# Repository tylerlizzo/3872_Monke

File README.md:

# Monke
# File Structure

CAD - Includes files for 3D printed parts of the monkey

Docs - Relevant documentation for creating your own monkey

Firmware - Signal processing, selection of octave, manual control

Hardware - Arduino UNO shield for power distribution, motor control, microphone and speaker amplification, and digital-to-audio conversion

Production - Gerber files for board production and .stl files for enclosure

Simulation - Relevant files for verification of hardware

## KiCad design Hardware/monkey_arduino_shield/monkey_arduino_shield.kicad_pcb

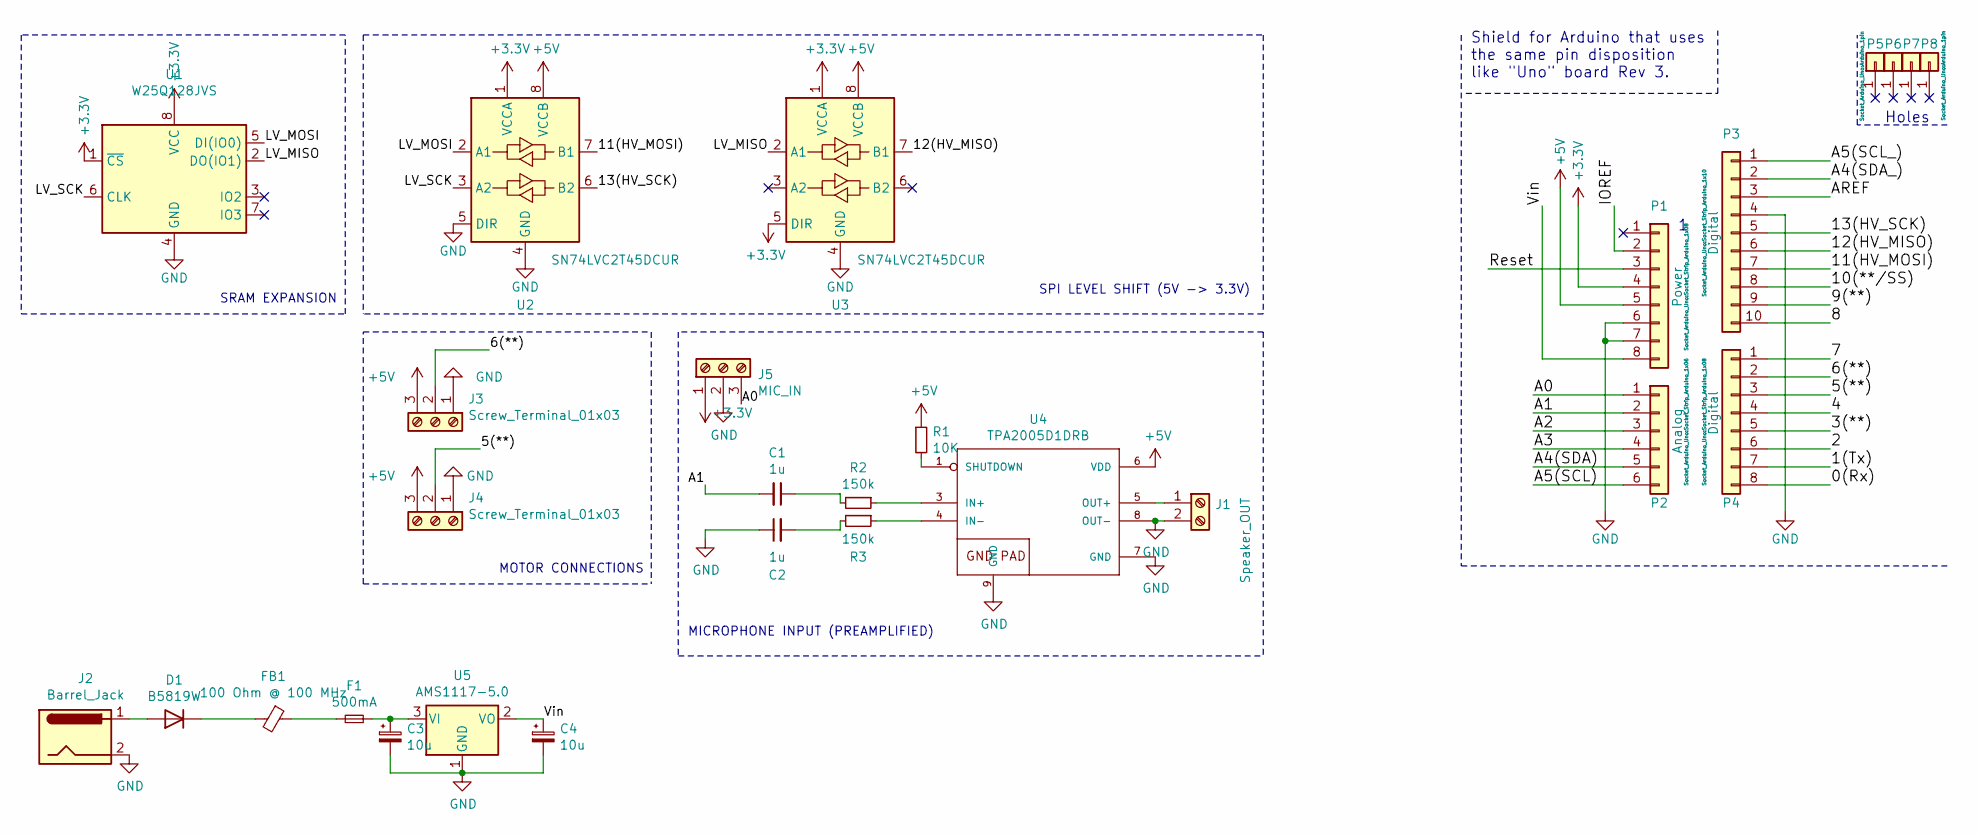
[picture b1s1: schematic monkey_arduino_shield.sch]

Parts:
C1, C2: 1u; C_1206_3216Metric
C3, C4: 10u; C_1206_3216Metric
D1: B5819W; D_0603_1608Metric
F1: 500mA; Fuse_0603_1608Metric
FB1: 100 Ohm @ 100 MHz; L_0201_0603Metric
J1: Speaker_OUT; TerminalBlock_bornier-2_P5.08mm
J2: Barrel_Jack; BarrelJack_Horizontal
J3, J4: Screw_Terminal_01x03; TerminalBlock_bornier-3_P5.08mm
J5: MIC_IN; TerminalBlock_bornier-3_P5.08mm
P1: Power; Socket_Strip_Arduino_1x08
P2: Analog; Socket_Strip_Arduino_1x06
P3: Digital; Socket_Strip_Arduino_1x10
P4: Digital; Socket_Strip_Arduino_1x08
P5, P6, P7, P8: CONN_01X01; Arduino_1pin
R1: 10K; R_0603_1608Metric
R2, R3: 150k; R_0603_1608Metric
U1: W25Q128JVS; SOIC-8_5.23x5.23mm_P1.27mm
U2, U3: SN74LVC2T45DCUR; VSSOP-8_2.4x2.1mm_P0.5mm
U4: TPA2005D1DRB; MSOP-8-1EP_3x3mm_P0.65mm_EP1.68x1.88mm
U5: AMS1117-5.0; SOT-223-3_TabPin2

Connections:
+3V3: J5.1, P1.4, U1.1 (~CS), U1.8 (VCC), U2.1 (VCCA), U3.1 (VCCA), U3.5 (DIR)
+5V: J3.3, J4.3, P1.5, R1.1, U2.8 (VCCB), U3.8 (VCCB), U4.6 (VDD)
/0(Rx): P4.8
/1(Tx): P4.7
/2: P4.6
/3(**): P4.5
/4: P4.4
/5(**): J4.2, P4.3
/6(**): J3.2, P4.2
/7: P4.1
/8: P3.10
/9(**): P3.9
/10(**/SS): P3.8
/11(HV_MOSI): P3.7, U2.7 (B1)
/12(HV_MISO): P3.6, U3.7 (B1)
/13(HV_SCK): P3.5, U2.6 (B2)
/A0: J5.3, P2.1
/A1: C1.2, P2.2
/A2: P2.3
/A3: P2.4
/A4(SDA): P2.5
/A4(SDA_): P3.2
/A5(SCL): P2.6
/A5(SCL_): P3.1
/AREF: P3.3
/IOREF: P1.2
/LV_MISO: U1.2 (DO(IO1)), U3.2 (A1)
/LV_MOSI: U1.5 (DI(IO0)), U2.2 (A1)
/LV_SCK: U1.6 (CLK), U2.3 (A2)
/Reset: P1.3
/Vin: C4.1, P1.8, U5.2 (VO)
GND: C2.1, C3.2, C4.2, J1.2, J2.2, J3.1, J4.1, J5.2, P1.6, P1.7, P3.4, U1.4 (GND), U2.4 (GND), U2.5 (DIR), U3.4 (GND), U4.7 (GND), U4.8 (OUT-), U4.9 (GND), U4.10 (GND), U4.11 (GND), U4.12 (GND), U4.13 (GND), U5.1 (GND)
unnamed: C1.1, R2.2
unnamed: C2.2, R3.2
unnamed: C3.1, F1.2, U5.3 (VI)
unnamed: D1.1 (K), FB1.2
unnamed: D1.2 (A), J2.1
unnamed: F1.1, FB1.1
unnamed: J1.1, U4.5 (OUT+)
unnamed: R1.2, U4.1 (SHUTDOWN)
unnamed: R2.1, U4.3 (IN+)
unnamed: R3.1, U4.4 (IN-)

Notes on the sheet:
Holes
Shield for Arduino that uses the same pin disposition like "Uno" board Rev 3.
SRAM EXPANSION
SPI LEVEL SHIFT (5V -> 3.3V)
MOTOR CONNECTIONS
MICROPHONE INPUT (PREAMPLIFIED)

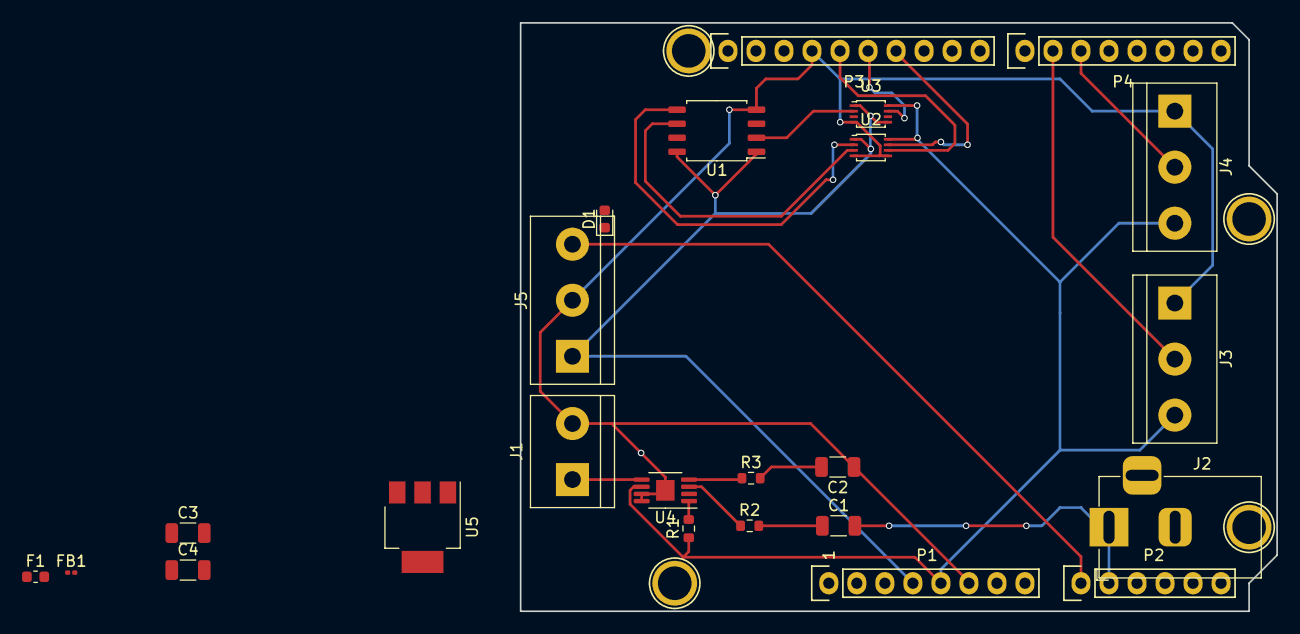
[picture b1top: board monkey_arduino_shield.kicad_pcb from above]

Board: 2 copper layers, 68.6 x 53.3 mm, 28 parts (0 on the bottom side), 24 nets.

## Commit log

2021-08-31 Initial Commit
    Added folder structure
2021-08-31 Added folders
2021-09-01 Added 3872_monkey_diagram
2021-09-01 Update 3872_monkey_diagram
2021-09-01 Added BOM
2021-09-21 First Hardware Rev
    Added RAM, motor drivers, audio I/O
2021-09-21 Added power handling to schematic.
